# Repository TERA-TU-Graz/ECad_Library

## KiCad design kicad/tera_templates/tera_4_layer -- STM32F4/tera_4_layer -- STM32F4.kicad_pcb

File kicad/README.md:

# Sources for footpritns and symbols lib.

Most symbols and footprints are either directly taken from the [official
Kicad library](https://github.com/KiCad) (and modified to fit the convention of this project)
or generated via the [footprint generator scripts](https://github.com/pointhi/kicad-footprint-generator).

For this reason the footprints and symbols are under GPLv2

# Sources for 3d models.

Most [3d models are script generated](https://github.com/easyw/kicad-3d-models-in-freecad). (using the same generators as the official kicad lib)
Some models are created directly with freecad.

The more useful models have been shared with the [official packages3d lib](https://github.com/KiCad/packages3D/) of kicad. For this reason they are under GPLv2 with the "symbol exception".
See: https://github.com/KiCad/packages3D/wiki/Model-Licencing

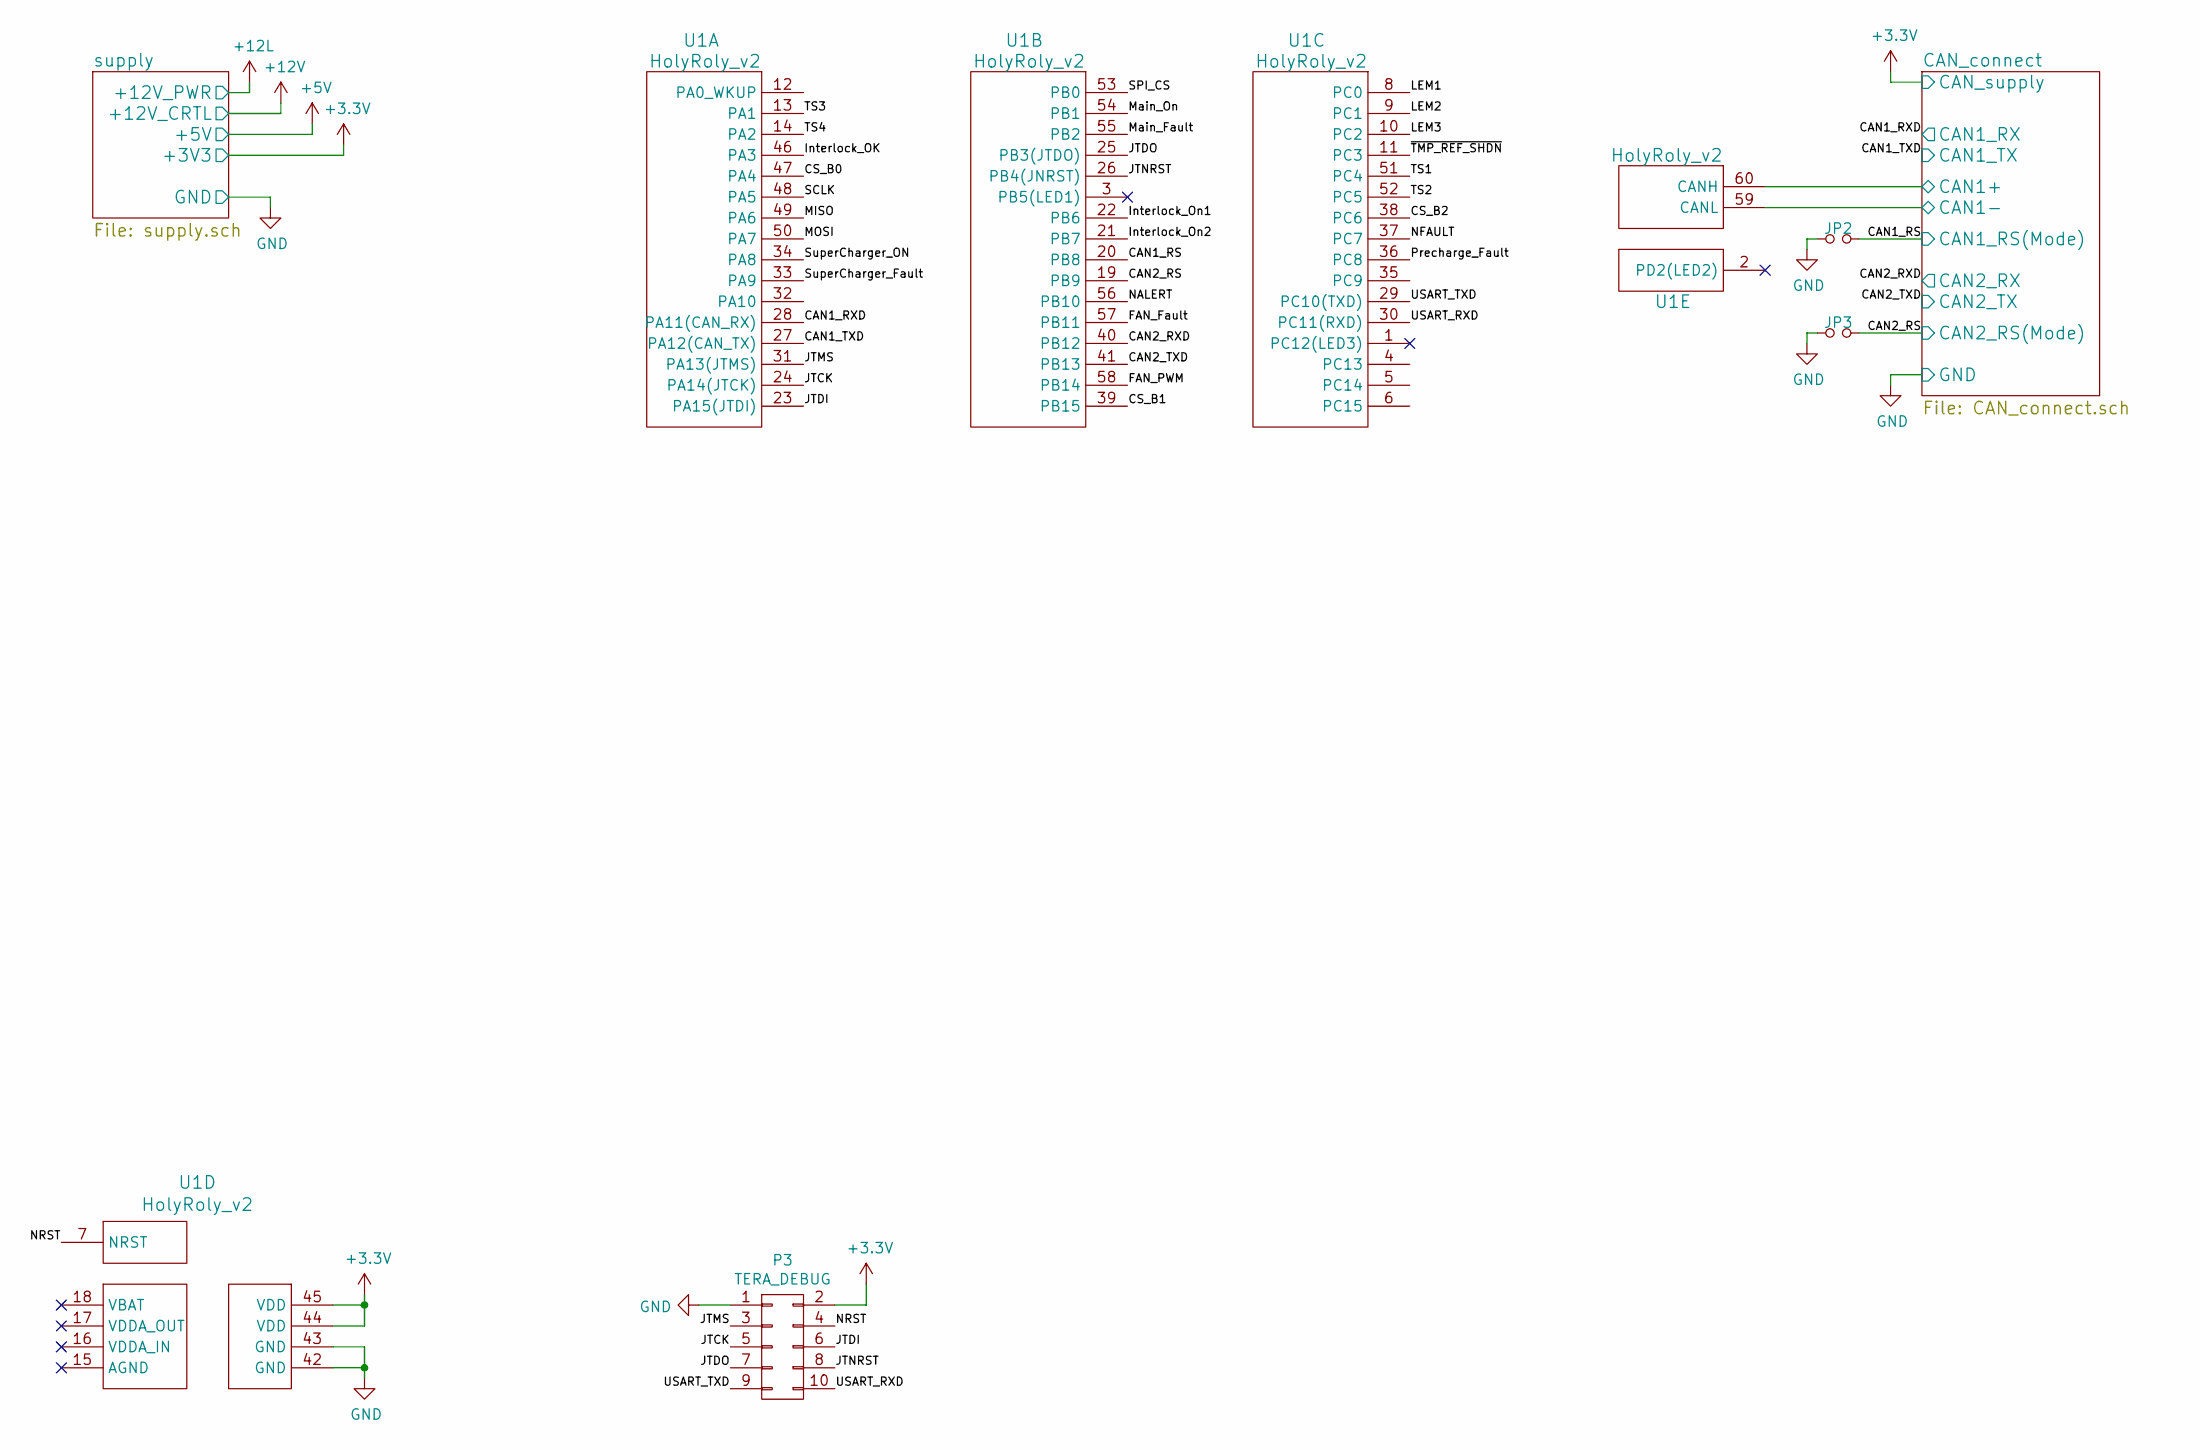
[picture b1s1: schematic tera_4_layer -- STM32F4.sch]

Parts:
JP2, JP3: Jumper_NO_Small; SOLDERJUMPER_2
P3: TERA_DEBUG
U1: HolyRoly_v2

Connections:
+3V3: P3.2, U1.44 (VDD), U1.45 (VDD); also elsewhere on the board
/CAN1_RS: JP2.2, U1.20 (PB8); also elsewhere on the board
/CAN1_RXD: U1.28 (PA11(CAN_RX)); also elsewhere on the board
/CAN1_TXD: U1.27 (PA12(CAN_TX)); also elsewhere on the board
/CAN2_RS: JP3.2, U1.19 (PB9); also elsewhere on the board
/CAN2_RXD: U1.40 (PB12); also elsewhere on the board
/CAN2_TXD: U1.41 (PB13); also elsewhere on the board
/CAN_connect/CAN1+: U1.60 (CANH); also elsewhere on the board
/CAN_connect/CAN1-: U1.59 (CANL); also elsewhere on the board
/CS_B0: U1.47 (PA4)
/CS_B1: U1.39 (PB15)
/CS_B2: U1.38 (PC6)
/FAN_Fault: U1.57 (PB11)
/FAN_PWM: U1.58 (PB14)
/Interlock_OK: U1.46 (PA3)
/Interlock_On1: U1.22 (PB6)
/Interlock_On2: U1.21 (PB7)
/JTCK: P3.5, U1.24 (PA14(JTCK))
/JTDI: P3.6, U1.23 (PA15(JTDI))
/JTDO: P3.7, U1.25 (PB3(JTDO))
/JTMS: P3.3, U1.31 (PA13(JTMS))
/JTNRST: P3.8, U1.26 (PB4(JNRST))
/LEM1: U1.8 (PC0)
/LEM2: U1.9 (PC1)
/LEM3: U1.10 (PC2)
/MISO: U1.49 (PA6)
/MOSI: U1.50 (PA7)
/Main_Fault: U1.55 (PB2)
/Main_On: U1.54 (PB1)
/NALERT: U1.56 (PB10)
/NFAULT: U1.37 (PC7)
/NRST: P3.4, U1.7 (NRST)
/Precharge_Fault: U1.36 (PC8)
/SCLK: U1.48 (PA5)
/SPI_CS: U1.53 (PB0)
/SuperCharger_Fault: U1.33 (PA9)
/SuperCharger_ON: U1.34 (PA8)
/TS1: U1.51 (PC4)
/TS2: U1.52 (PC5)
/TS3: U1.13 (PA1)
/TS4: U1.14 (PA2)
/USART_RXD: P3.10, U1.30 (PC11(RXD))
/USART_TXD: P3.9, U1.29 (PC10(TXD))
/~TMP_REF_SHDN: U1.11 (PC3)
GND: JP2.1, JP3.1, P3.1, U1.42 (GND), U1.43 (GND); also elsewhere on the board

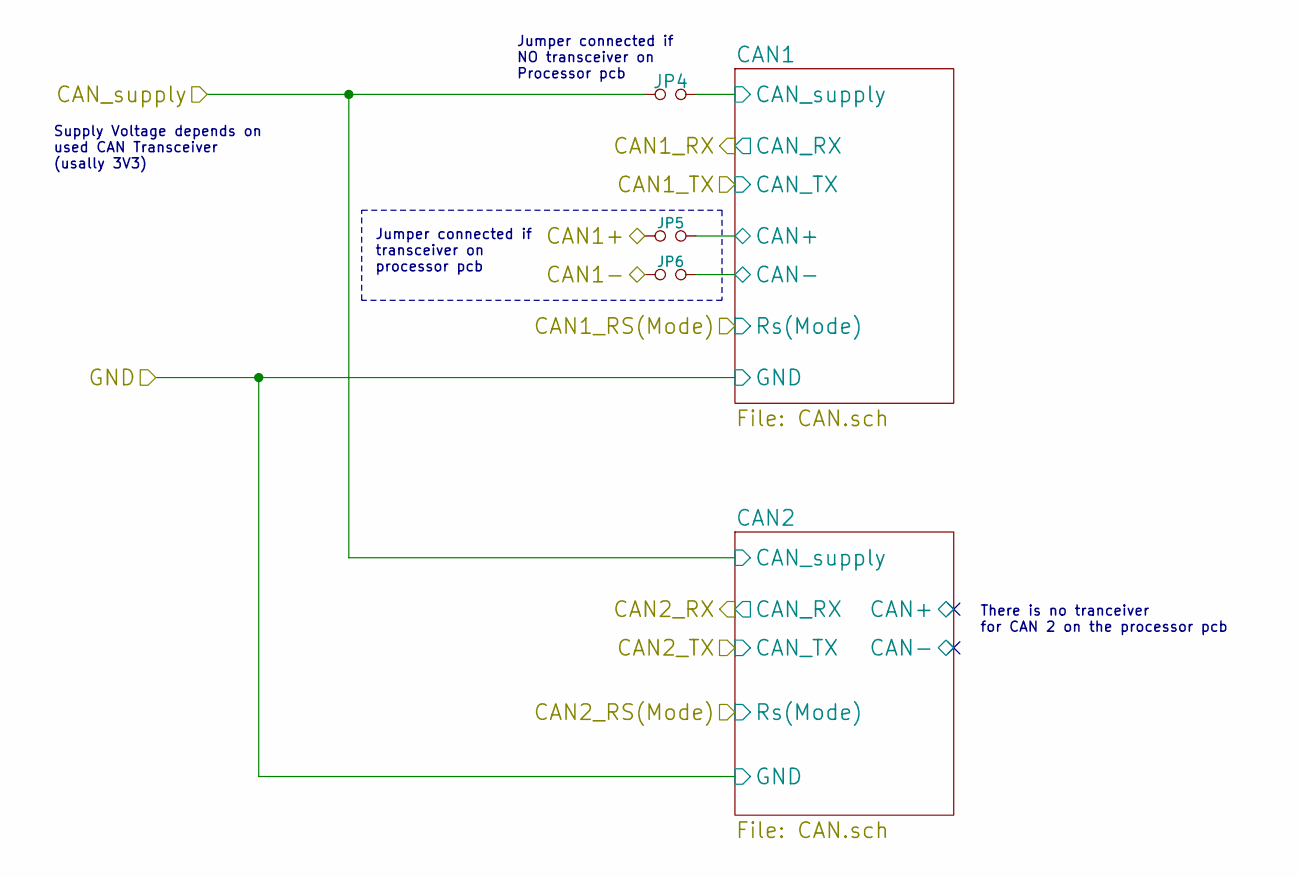
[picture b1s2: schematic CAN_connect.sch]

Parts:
JP4, JP5, JP6: Jumper_NO_Small; SOLDERJUMPER_2

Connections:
+3V3: JP4.1; also elsewhere on the board
/CAN_connect/CAN1+: JP5.1; also elsewhere on the board
/CAN_connect/CAN1-: JP6.1; also elsewhere on the board
/CAN_connect/CAN1/CAN+: JP5.2; also elsewhere on the board
/CAN_connect/CAN1/CAN-: JP6.2; also elsewhere on the board
/CAN_connect/CAN1/CAN_supply: JP4.2; also elsewhere on the board

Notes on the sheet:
Supply Voltage depends on used CAN Transceiver (usally 3V3)
Jumper connected if NO transceiver on Processor pcb
Jumper connected if transceiver on processor pcb
There is no tranceiver for CAN 2 on the processor pcb

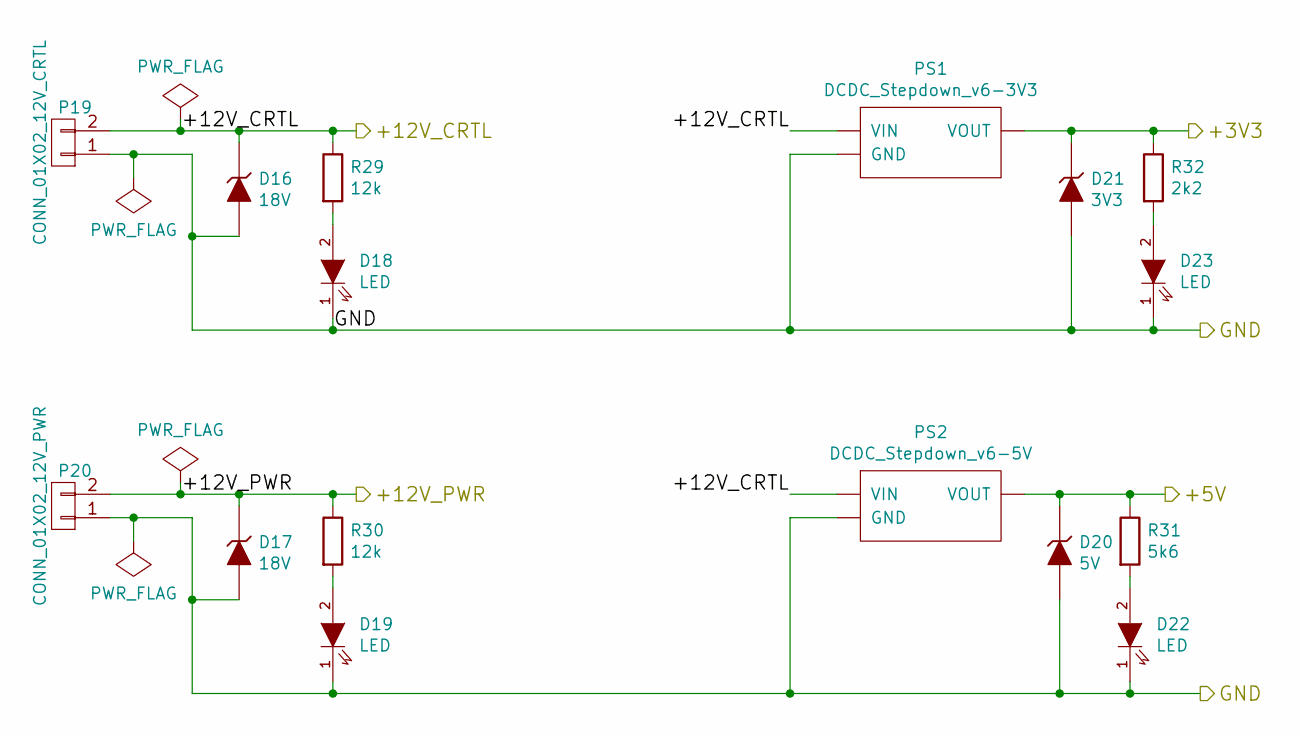
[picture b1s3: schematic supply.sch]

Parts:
D16, D17: 18V; DO-214AA_with_vias_in_pad
D18, D19, D22, D23: LED; LED_0805
D20: 5V; DO-216AA
D21: 3V3; DO-216AA
P19: CONN_01X02_12V_CRTL; JST_XH_B02B-XH-A_02x2.50mm_Straight
P20: CONN_01X02_12V_PWR; MCV_1.5_2-GF-3.5
PS1: DCDC_Stepdown_v6-3V3; DCDC_Stepdown_v6
PS2: DCDC_Stepdown_v6-5V; DCDC_Stepdown_v6
R29, R30: 12k; C_0805in
R31: 5k6; C_0805in
R32: 2k2; C_0805in

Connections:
+3V3: D21.1 (K), PS1.2 (VOUT), R32.1; also elsewhere on the board
+5V: D20.1 (K), PS2.2 (VOUT), R31.1
+12L: D17.1 (K), P20.2, R30.1
+12V: D16.1 (K), P19.2, PS1.1 (VIN), PS2.1 (VIN), R29.1
GND: D16.2 (A), D17.2 (A), D18.1 (K), D19.1 (K), D20.2 (A), D21.2 (A), D22.1 (K), D23.1 (K), P19.1, P20.1, PS1.3 (GND), PS1.4 (GND), PS2.3 (GND), PS2.4 (GND); also elsewhere on the board
unnamed: D18.2 (A), R29.2
unnamed: D19.2 (A), R30.2
unnamed: D22.2 (A), R31.2
unnamed: D23.2 (A), R32.2

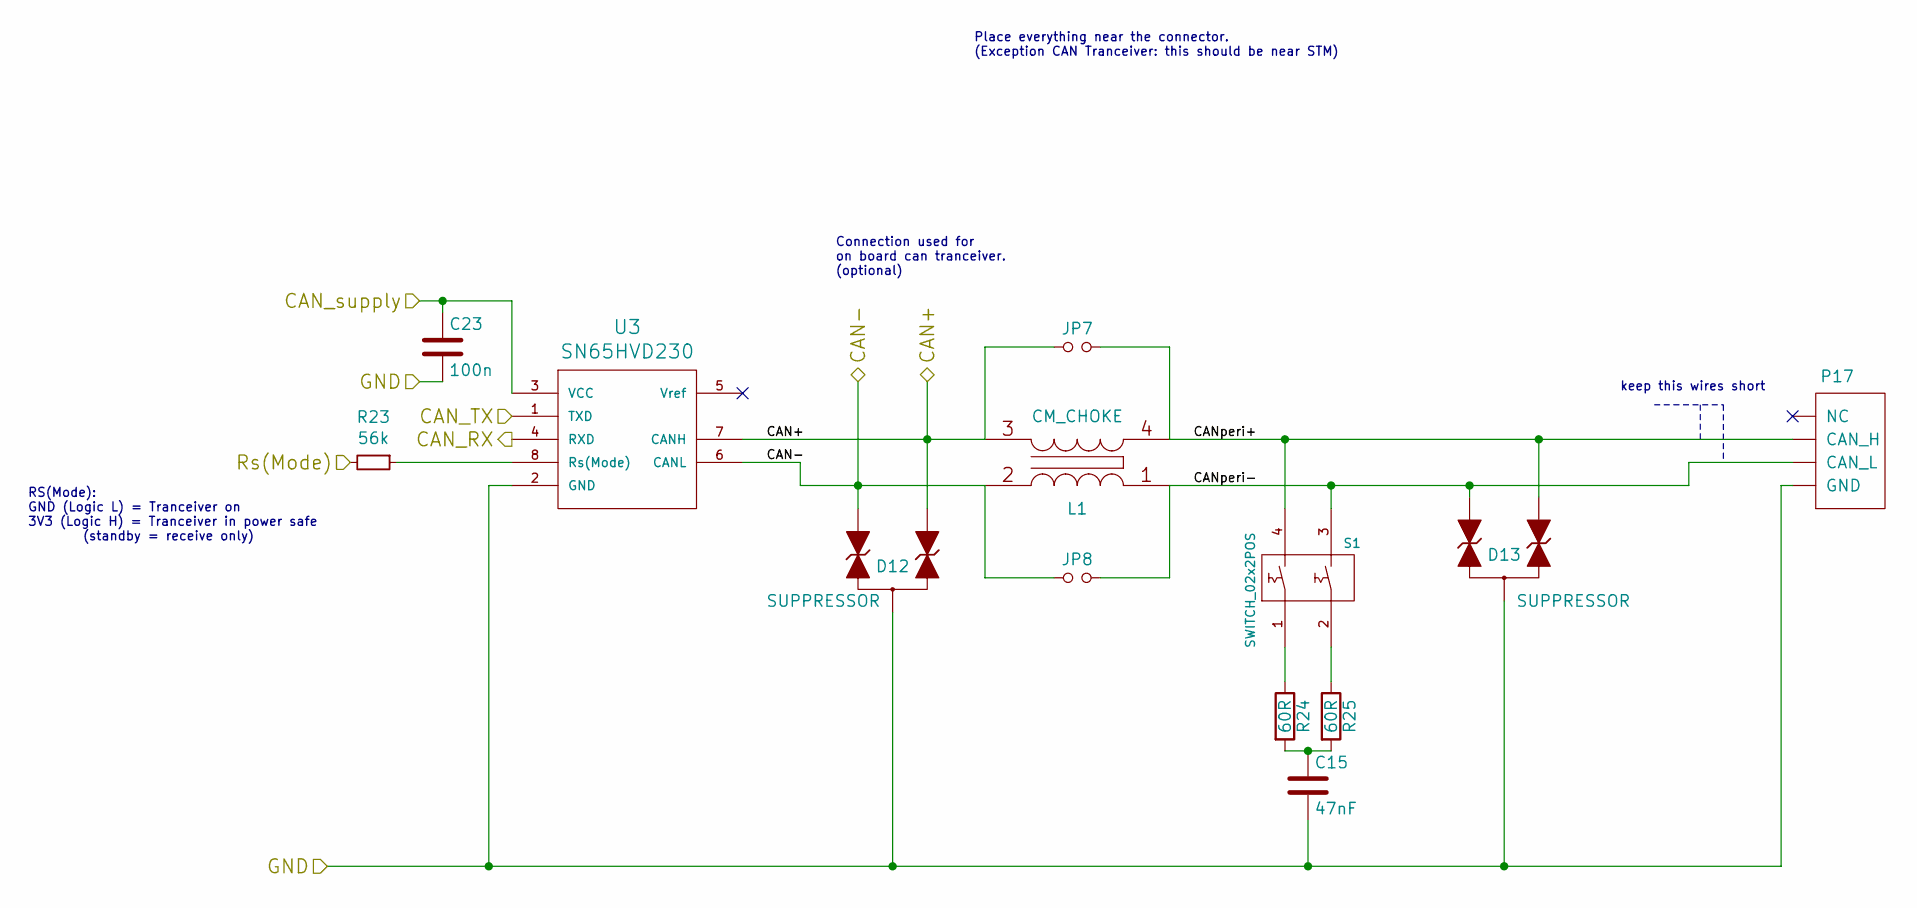
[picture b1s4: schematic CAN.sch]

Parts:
C15: 47nF; C_0805in
C23: 100n; C_0805in
D12, D13: SUPPRESSOR; SOT-23
JP7, JP8: Jumper_NO_Small; SOLDERJUMPER_2
L1: CM_CHOKE; L_ACT45B-XXX-2P_common-mode-choke
P17: CAN_CON; CIOC_4-1-FV
R23: 56k; C_0805in
R24, R25: 60R; C_0805in
S1: SWITCH_02x2POS; TE_1825360-1
U3: SN65HVD230

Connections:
/CAN1_RS: R23.2; also elsewhere on the board
/CAN1_RXD: U3.4 (RXD); also elsewhere on the board
/CAN1_TXD: U3.1 (TXD); also elsewhere on the board
/CAN_connect/CAN1/CAN+: D12.2 (Pin2), JP7.1, L1.3 (SA), U3.7 (CANH); also elsewhere on the board
/CAN_connect/CAN1/CAN-: D12.1 (Pin1), JP8.1, L1.2 (AB), U3.6 (CANL); also elsewhere on the board
/CAN_connect/CAN1/CAN_supply: C23.1, U3.3 (VCC); also elsewhere on the board
/CAN_connect/CAN1/CANperi+: D13.2 (Pin2), JP7.2, L1.4 (SB), P17.3 (CAN_H), S1.4
/CAN_connect/CAN1/CANperi-: D13.1 (Pin1), JP8.2, L1.1 (AA), P17.2 (CAN_L), S1.3
GND: C15.2, C23.2, D12.3 (Pin3), D13.3 (Pin3), P17.1 (GND), U3.2 (GND); also elsewhere on the board
unnamed: C15.1, R24.2, R25.2
unnamed: R23.1, U3.8 (Rs(Mode))
unnamed: R24.1, S1.1
unnamed: R25.1, S1.2

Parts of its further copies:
C16: 47nF; C_0805in
C24: 100n; C_0805in
D14, D15: SUPPRESSOR; SOT-23
JP9, JP10: Jumper_NO_Small; SOLDERJUMPER_2
L2: CM_CHOKE; L_ACT45B-XXX-2P_common-mode-choke
P18: CAN_CON; CIOC_4-1-FV
R26: 56k; C_0805in
R27, R28: 60R; C_0805in
S2: SWITCH_02x2POS; TE_1825360-1
U4: SN65HVD230

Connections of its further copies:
+3V3: C24.1, U4.3 (VCC); also elsewhere on the board
/CAN2_RS: R26.2; also elsewhere on the board
/CAN2_RXD: U4.4 (RXD); also elsewhere on the board
/CAN2_TXD: U4.1 (TXD); also elsewhere on the board
/CAN_connect/CAN2/CAN+: D14.2 (Pin2), JP9.1, L2.3 (SA), U4.7 (CANH)
/CAN_connect/CAN2/CAN-: D14.1 (Pin1), JP10.1, L2.2 (AB), U4.6 (CANL)
/CAN_connect/CAN2/CANperi+: D15.2 (Pin2), JP9.2, L2.4 (SB), P18.3 (CAN_H), S2.4
/CAN_connect/CAN2/CANperi-: D15.1 (Pin1), JP10.2, L2.1 (AA), P18.2 (CAN_L), S2.3
GND: C16.2, C24.2, D14.3 (Pin3), D15.3 (Pin3), P18.1 (GND), U4.2 (GND); also elsewhere on the board
unnamed: C16.1, R27.2, R28.2
unnamed: R26.1, U4.8 (Rs(Mode))
unnamed: R27.1, S2.1
unnamed: R28.1, S2.2

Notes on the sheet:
RS(Mode): GND (Logic L) = Tranceiver on 3V3 (Logic H) = Tranceiver in power safe (standby = receive only)
Connection used for on board can tranceiver. (optional)
Place everything near the connector. (Exception CAN Tranceiver: this should be near STM)
keep this wires short

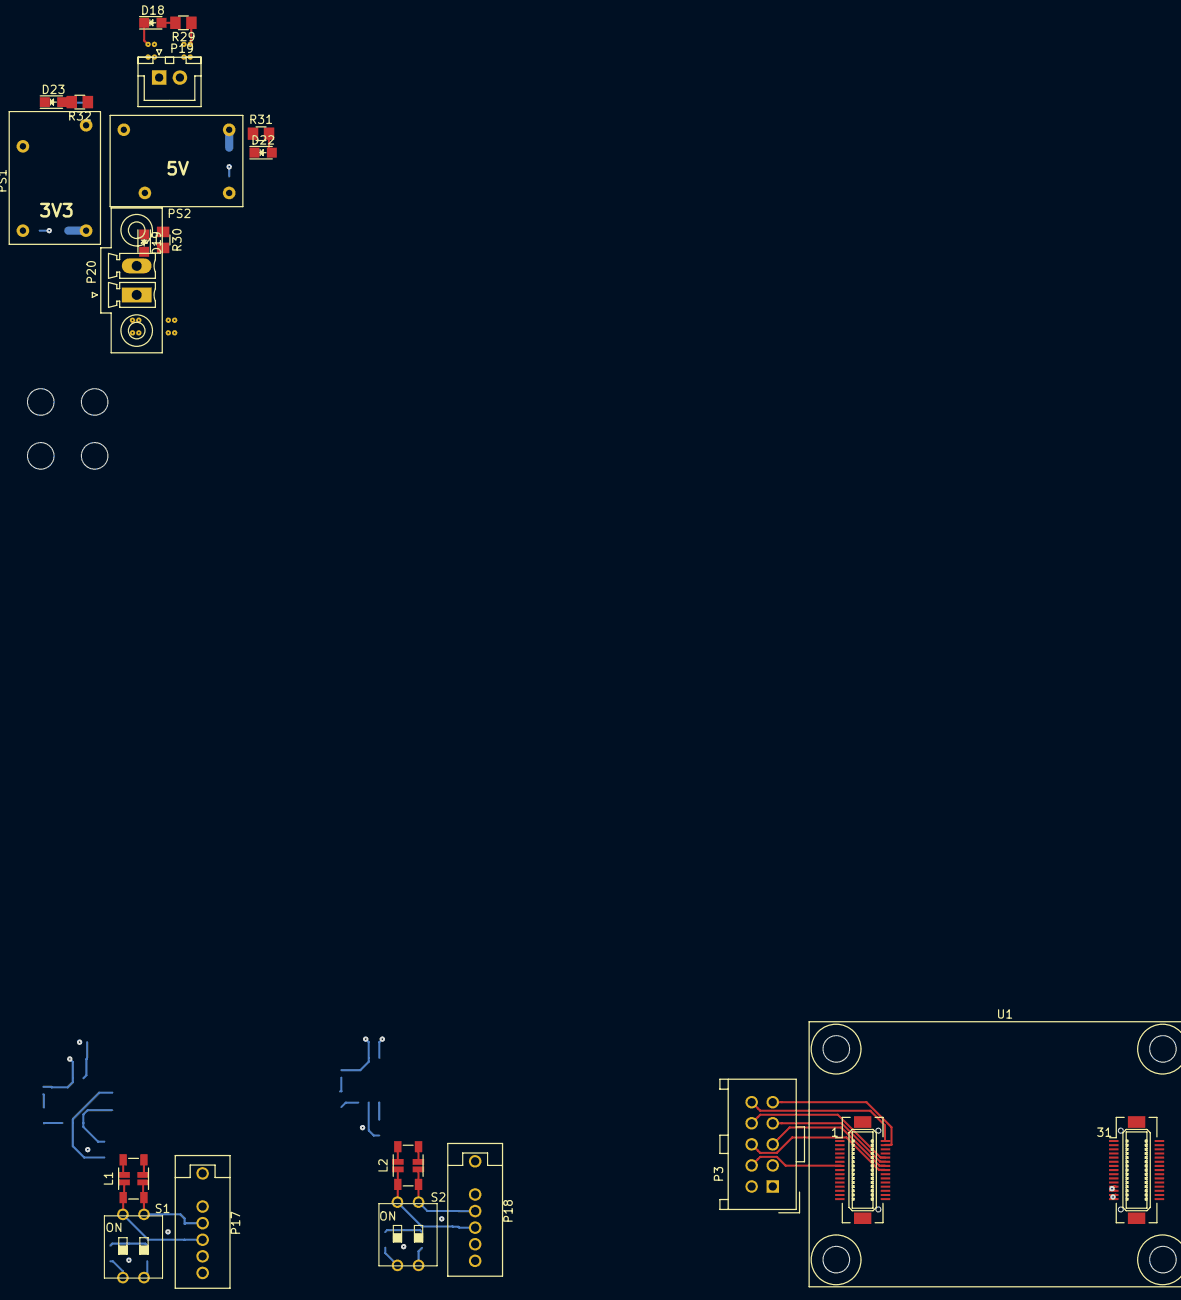
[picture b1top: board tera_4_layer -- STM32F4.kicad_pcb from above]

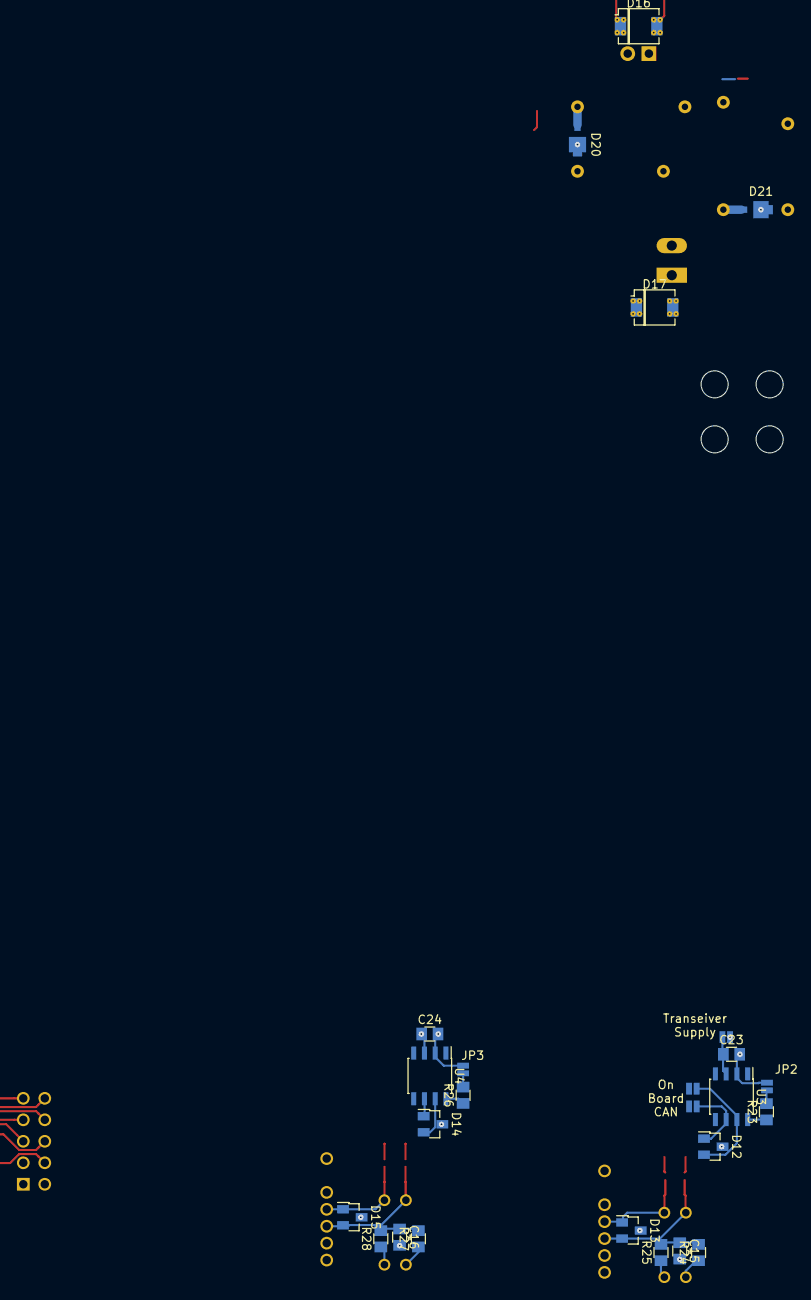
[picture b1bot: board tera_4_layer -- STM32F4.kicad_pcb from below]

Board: 4 copper layers, 49 parts (25 on the bottom side), 42 nets.

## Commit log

2017-08-10 Initial commit, adding everything we have
2017-08-10 Licensing of kicad libs
2018-10-28 Sync github kicad libs with tera local libs
